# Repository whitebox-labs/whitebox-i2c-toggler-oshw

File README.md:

# I2C Toggler

The I2C Toggler is a small device to assist in switching the bus mode of Atlas Scientific EZO circuits between UART and I2C.

The EZO circuits bus mode can be switched by shorting certain pins upon power-up of the EZO-circuit. Repeating the process will switch the modes between UART and I2C back and forth. Pins must be shorted before power-up and stay shorted. The EZO's LED will fade to another color (depending on mode).

The EZO RTD circuit is switched by shorting PRB to TX.
All other EZO circuits (pH, EC, DO, ORP) are switched by shorting PGND to TX.

The I2C Toggler has an EZO connector (two 1x3 female headers) to plug an EZO circuit. It has a tactile switch to select wether to operate on an RTD or another circuit (to select which pins get shorted). A momentary button, to actually power on the circuit and change its bus mode. The Bus Switcher itself is powered by plugging it into an USB port - the PCB itself is shaped like the inside of a male USB plug.

How to operate the I2C Toggler:
1. select EZO circuit type (RTD or other)
2. Put EZO circuit on to Bus Switcher
3. Plug Bus Switcher into USB-port
4. Press and hold button until EZO circuit boots up and changes the LED color
5. Release the button (which cuts power to the EZO circuit)

## License
Hardware design files and documentation are licensed under Attribution-ShareAlike 4.0 International (CC BY-SA 4.0)
https://creativecommons.org/licenses/by-sa/4.0/

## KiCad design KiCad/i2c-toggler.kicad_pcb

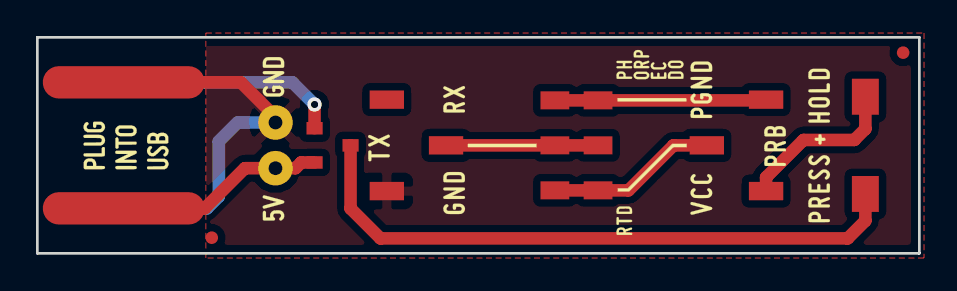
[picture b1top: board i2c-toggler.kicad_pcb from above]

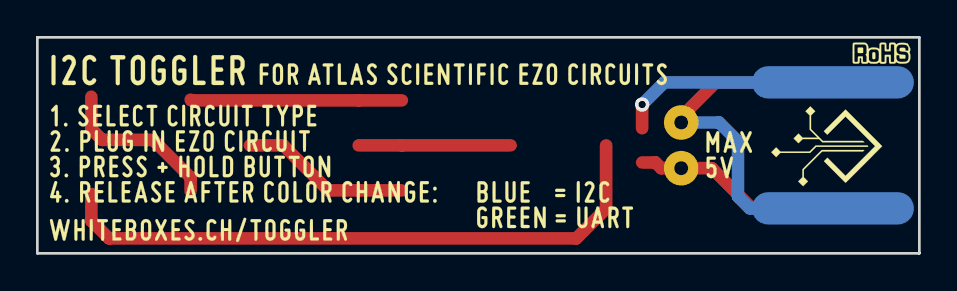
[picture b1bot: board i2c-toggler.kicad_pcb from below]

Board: 2 copper layers, 49.0 x 12.0 mm, 10 parts (2 on the bottom side), 8 nets.

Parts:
D101: BAT54C; WL-SOT23-3
GBOT: LOGO; WL-silks-BOT
GTOP: LOGO; WL-silks-TOP
P101: USB; WL-usb-A-TOP
P102: USB; WL-usb-A-BOT
STP101: ATLAS_STAMP; WL-EZO-13380
SW101: SW_PUSH; WL-WE434123043816
SW102: SW_SPDT; WL-JS202011JCQN
fiducial: VAL**; WL-fiducial_0.75mm
fiducial#2: VAL**; WL-fiducial_0.75mm

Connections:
/GND: P101.4, P102.4, STP101.1
/PGND: STP101.6, SW102.1
/PRB: STP101.5, SW102.3
/TX: STP101.2, SW102.2
/Vcc: D101.3, SW101.1
/VccBot: D101.1, P102.1
/VccTop: D101.2, P101.1
unnamed: STP101.4, SW101.2

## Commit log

2020-03-08 initial public commit

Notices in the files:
KiCad/i2c-toggler.kicad_pcb:
Licensed under a Creative Commons
